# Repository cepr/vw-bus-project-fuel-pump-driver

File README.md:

# vw-bus-project-fuel-pump-driver
Fuel pump driver interfaced on a LIN bus

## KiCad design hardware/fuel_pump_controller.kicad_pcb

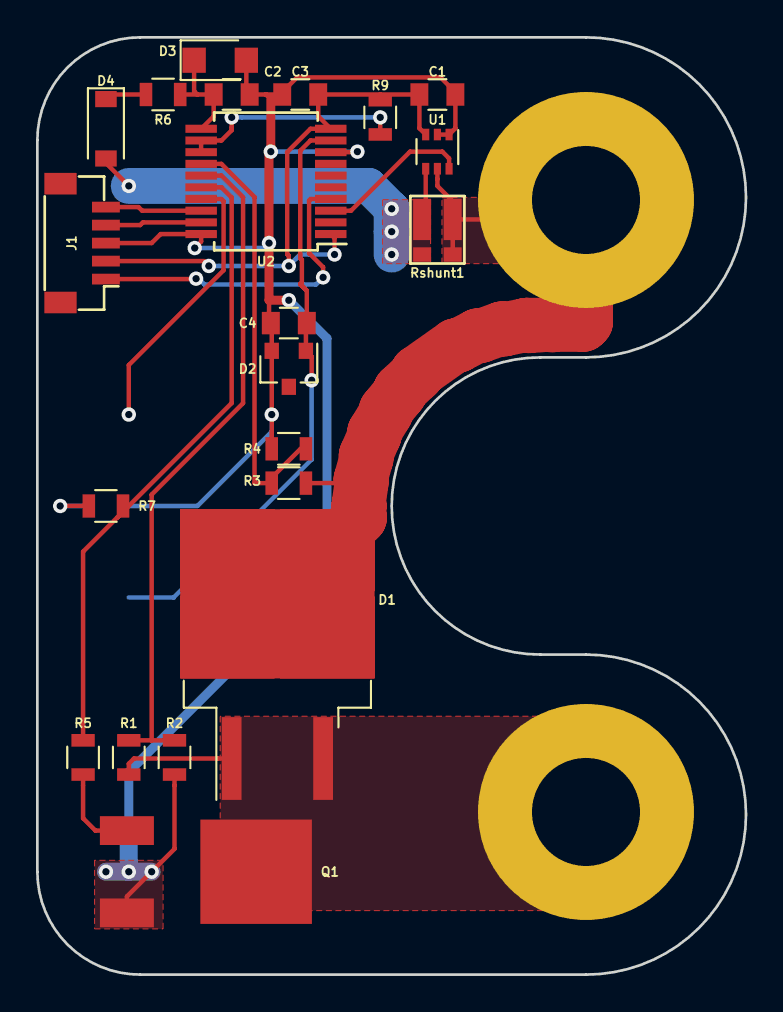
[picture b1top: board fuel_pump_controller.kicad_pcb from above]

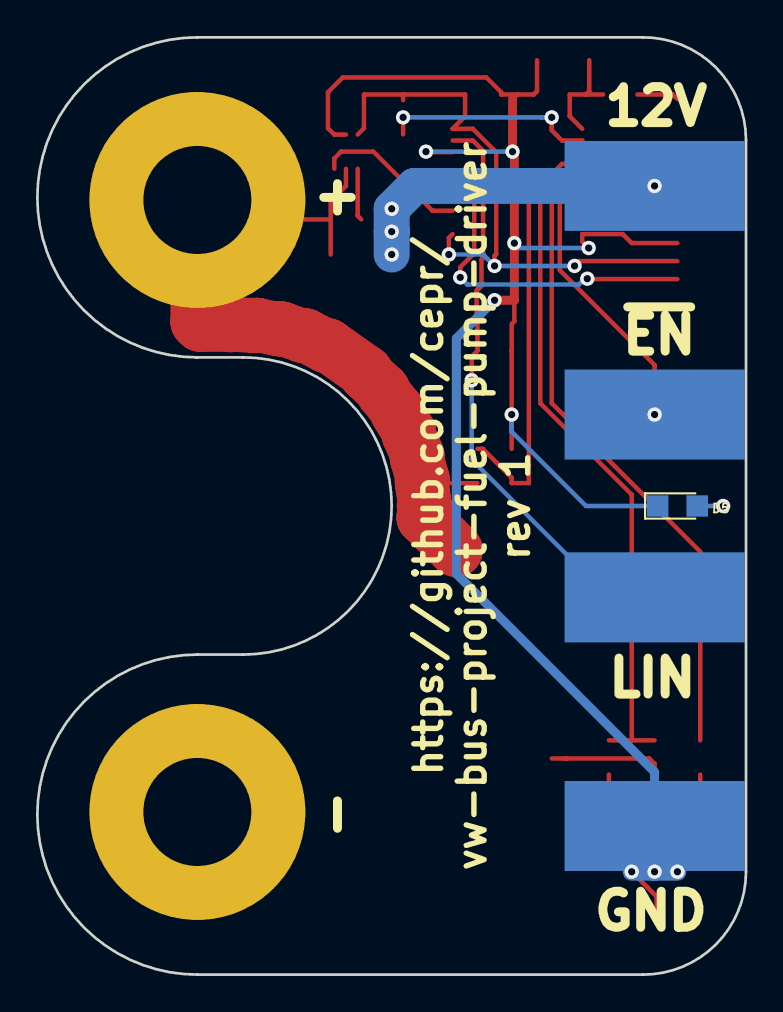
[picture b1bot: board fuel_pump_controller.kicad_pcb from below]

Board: 2 copper layers, 39.4 x 52.1 mm, 27 parts (5 on the bottom side), 19 nets.

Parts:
C1: 100n; C_0805
C2: 22uF; C_0805
C3: 10uF; C_0805
C4: 220p; C_0805
D1: VB30100S-E3/8W; TO-263-2
D2: MMBZ27V; SOT-23
D3: D_Schottky; D_SMF
D4: 1N4148; D_SOD-123
D5: LED; LED_0805
J1: JST_BM05B-SRSS-TB(LF)(SN); JST_BM05B
J2: +12V; SolderWirePad_single_SMD_5x10mm
J3: EN; SolderWirePad_single_SMD_5x10mm
J4: LIN; SolderWirePad_single_SMD_5x10mm
J5: GND; SolderWirePad_single_SMD_5x10mm
M1: Motor_DC; fuel_pump
Q1: NCV8401BDTRKG; 369C
R1, R3: 22.1k; R_0805
R2, R4: 10.7k; R_0805
R5, R7: 150; R_0805
R6: 47; R_0805
R9: 10k; R_0805
Rshunt1: 750u; CST0612
U1: INA199x3_SC70; SOT-363_SC-70-6
U2: PIC16F1829LIN-ESS; SSOP-20_5.3x7.2mm_Pitch0.65mm

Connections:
+5V: C1.1, C3.2, J1.2, R9.2, U1.3, U2.1, U2.10
+12V: D4.2, J2.1, Rshunt1.1, U1.4
/Frontend/CURRENT_SENSE: U1.6, U2.3
/Frontend/EN: R5.2, R7.1, U2.16
/Frontend/OUT+: D1.2, M1.1, R3.1, Rshunt1.2, U1.5
/Frontend/OUT+SENSE: R3.2, R4.1, U2.14
/Frontend/OUT-: D1.1, D1.3, M1.2, Q1.2, R1.1
/Frontend/OUT-SENSE: R1.2, R2.1, U2.15
/MCU/EXT_EN: J3.1, U2.17
/MCU/ICSPCLK: J1.5, U2.18
/MCU/ICSPDAT: J1.4, U2.19
/MCU/LIN: C4.1, D2.1, J4.1, U2.9
/MCU/~MCLR: J1.1, U2.4
GND: C1.2, C2.2, C3.1, C4.2, D2.2, D3.2, D5.1, J1.3, J5.1, Q1.3, R2.2, R4.2, U1.1, U1.2, U2.8, U2.20
unnamed: C2.1, D3.1, R6.2, U2.11
unnamed: D4.1, R6.1
unnamed: D5.2, R7.2
unnamed: Q1.1, R5.1
unnamed: R9.1, U2.12, U2.13

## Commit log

2019-02-17 rev 1
2019-02-18 Adding license
2019-03-02 Updating FAB layer
